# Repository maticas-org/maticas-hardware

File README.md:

# maticas-hardware
Hardware branch of Maticas. Maticas is an  Automated hidroponic system. Project that seeks to create a fully automated hydroponic cultivation system using IoT, with a view to generating an agricultural revolution.

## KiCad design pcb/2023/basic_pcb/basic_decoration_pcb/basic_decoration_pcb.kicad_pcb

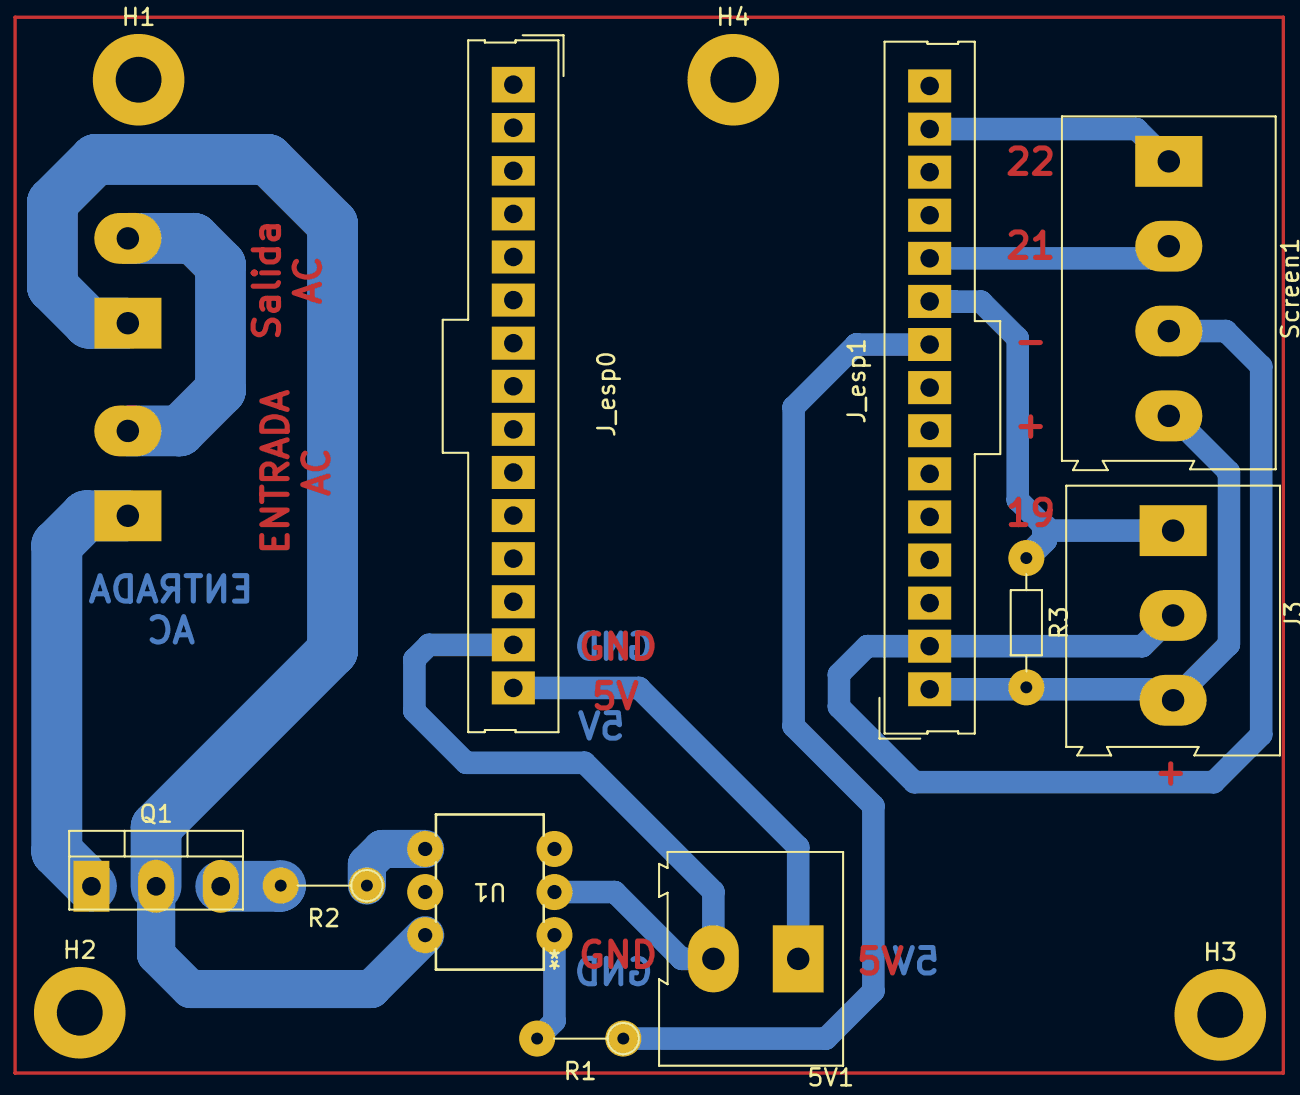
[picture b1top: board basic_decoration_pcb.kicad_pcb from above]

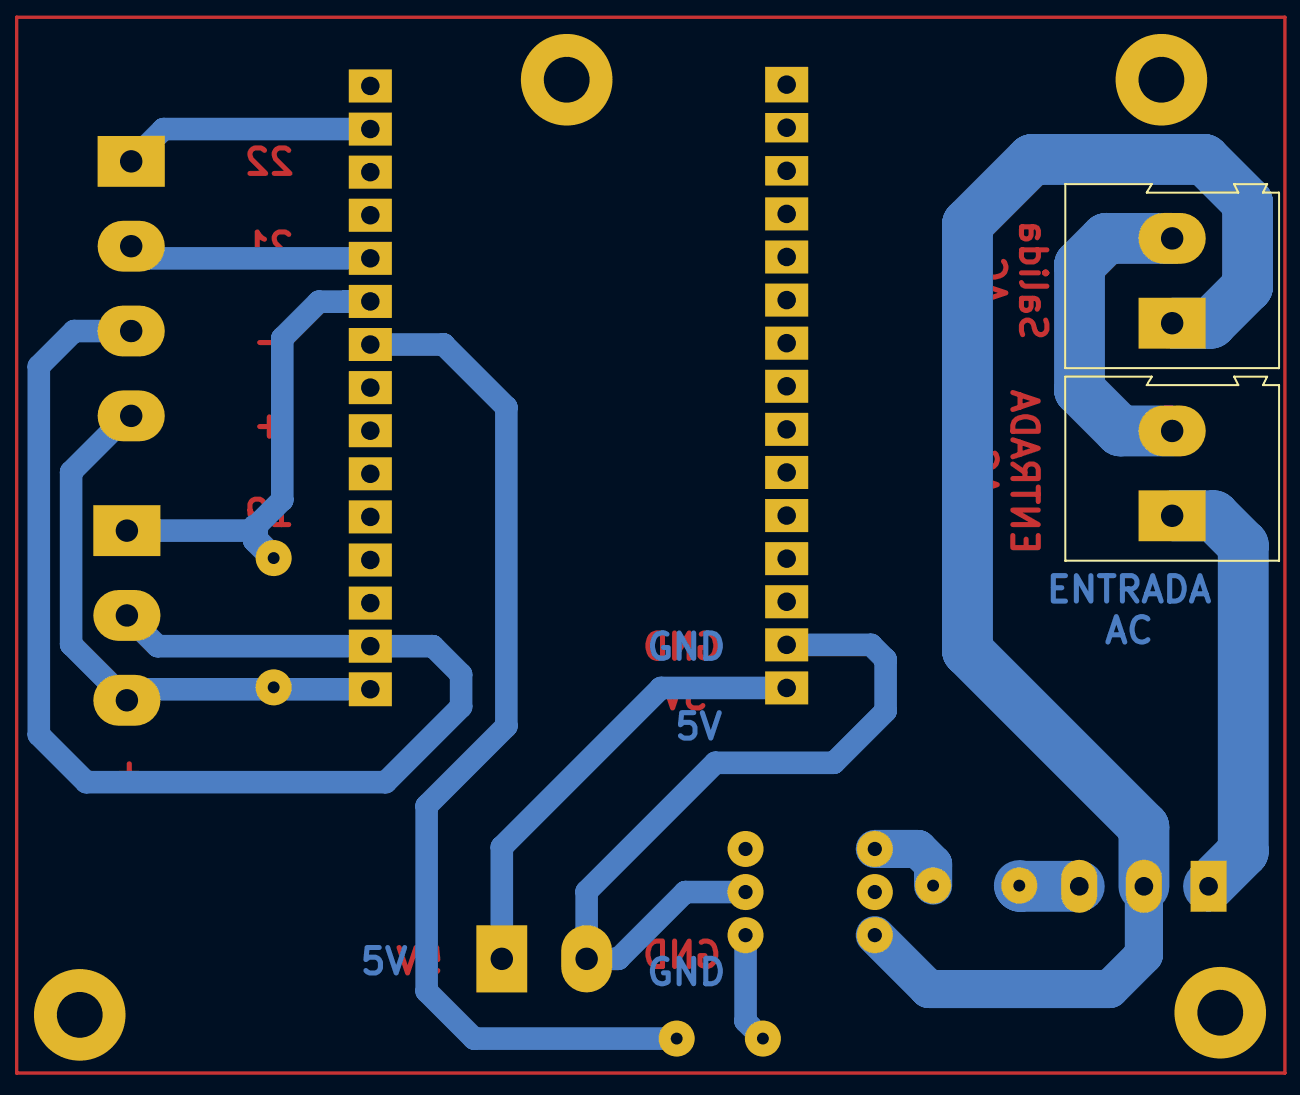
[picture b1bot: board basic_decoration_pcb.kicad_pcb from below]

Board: 2 copper layers, 16 parts (2 on the bottom side), 14 nets.

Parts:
5V1: Screw_Terminal_01x02; TerminalBlock_Altech_AK300-2_P5.00mm
H1, H2, H3, H4: MountingHole; MountingHole_2.7mm_M2.5_Pad
J3: Screw_Terminal_01x03; TerminalBlock_Altech_AK300-3_P5.00mm
J_AC_INPUT1: Screw_Terminal_01x02; TerminalBlock_Altech_AK300-2_P5.00mm
J_AC_LOAD1: Screw_Terminal_01x02; TerminalBlock_Altech_AK300-2_P5.00mm
J_esp0, J_esp1: Conn_01x15_Female; Connector_Molex_Molex_SL_171971-0015_1x15_P2.54mm_Vertical_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
Q1: BT136-500; TO-220-3_Vertical
R1, R2: 470; R_Axial_DIN0204_L3.6mm_D1.6mm_P5.08mm_Vertical
R3: 4.7k_0603; R_Axial_DIN0204_L3.6mm_D1.6mm_P7.62mm_Horizontal
Screen1: Screw_Terminal_01x04; TerminalBlock_Altech_AK300-4_P5.00mm
U1: MOC3041M; PDIP6_6P6X8P89_ONS

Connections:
3V3: J3.3, J_esp1.1, R3.2, Screen1.4
5v: 5V1.1, J_esp0.15
AC1_IN: J_AC_INPUT1.1, Q1.1 (A1)
AC2_IN: J_AC_INPUT1.2, J_AC_LOAD1.2
D18: J_esp1.9, R1.1
D19: J3.1, J_esp1.10, R3.1
D21: J_esp1.11, Screen1.2
D22: J_esp1.14, Screen1.1
GND2: J3.2, J_esp1.2, Screen1.3
GND5V: 5V1.2, J_esp0.14, U1.2
unnamed: J_AC_LOAD1.1, Q1.2 (A2), U1.6
unnamed: Q1.3 (G), R2.2
unnamed: R1.2, U1.1
unnamed: R2.1, U1.4

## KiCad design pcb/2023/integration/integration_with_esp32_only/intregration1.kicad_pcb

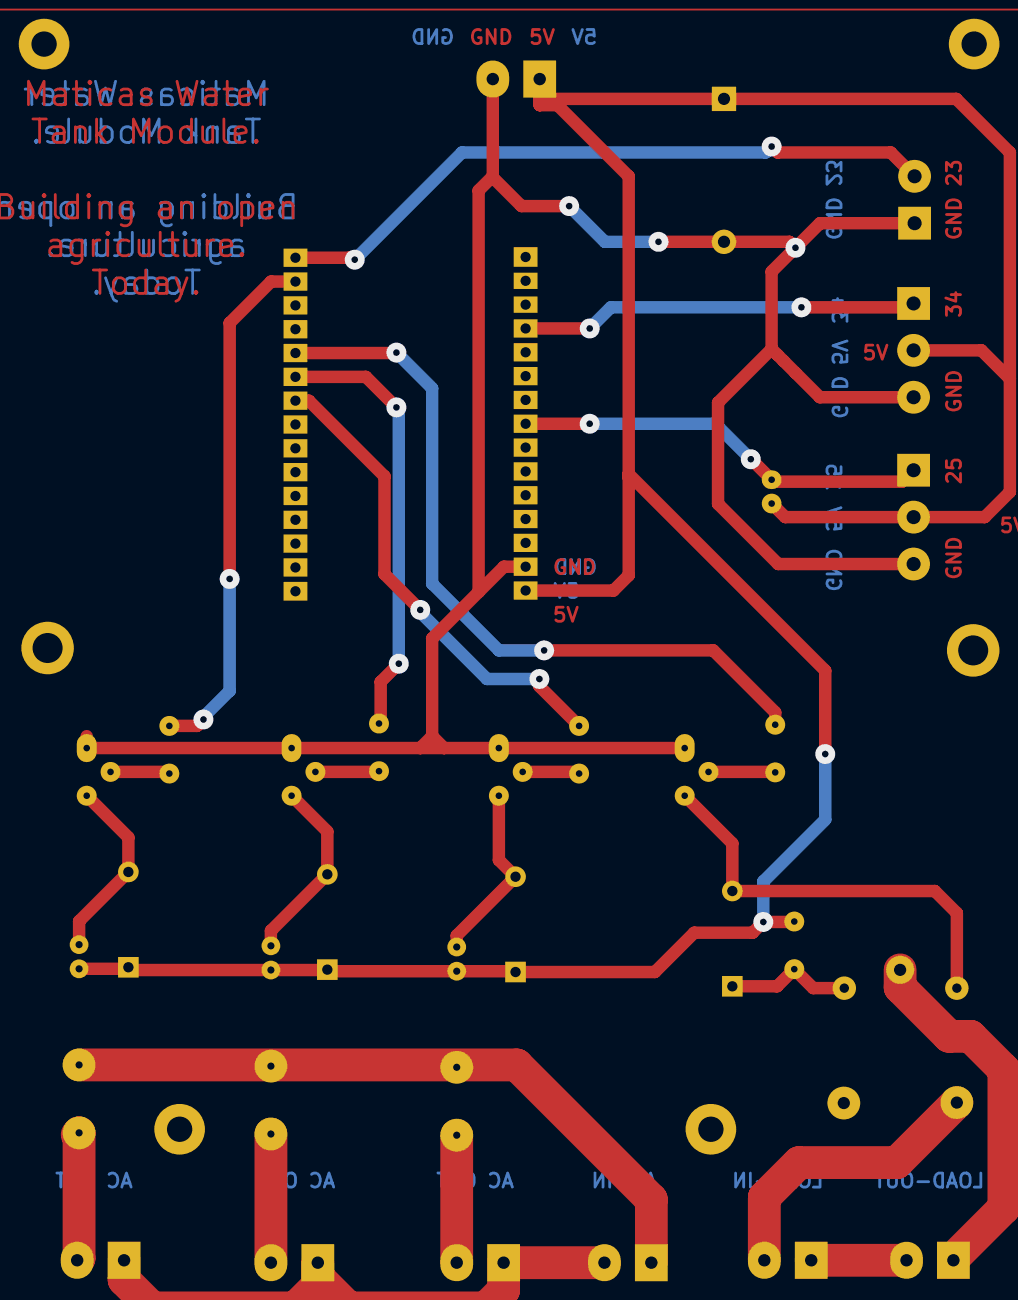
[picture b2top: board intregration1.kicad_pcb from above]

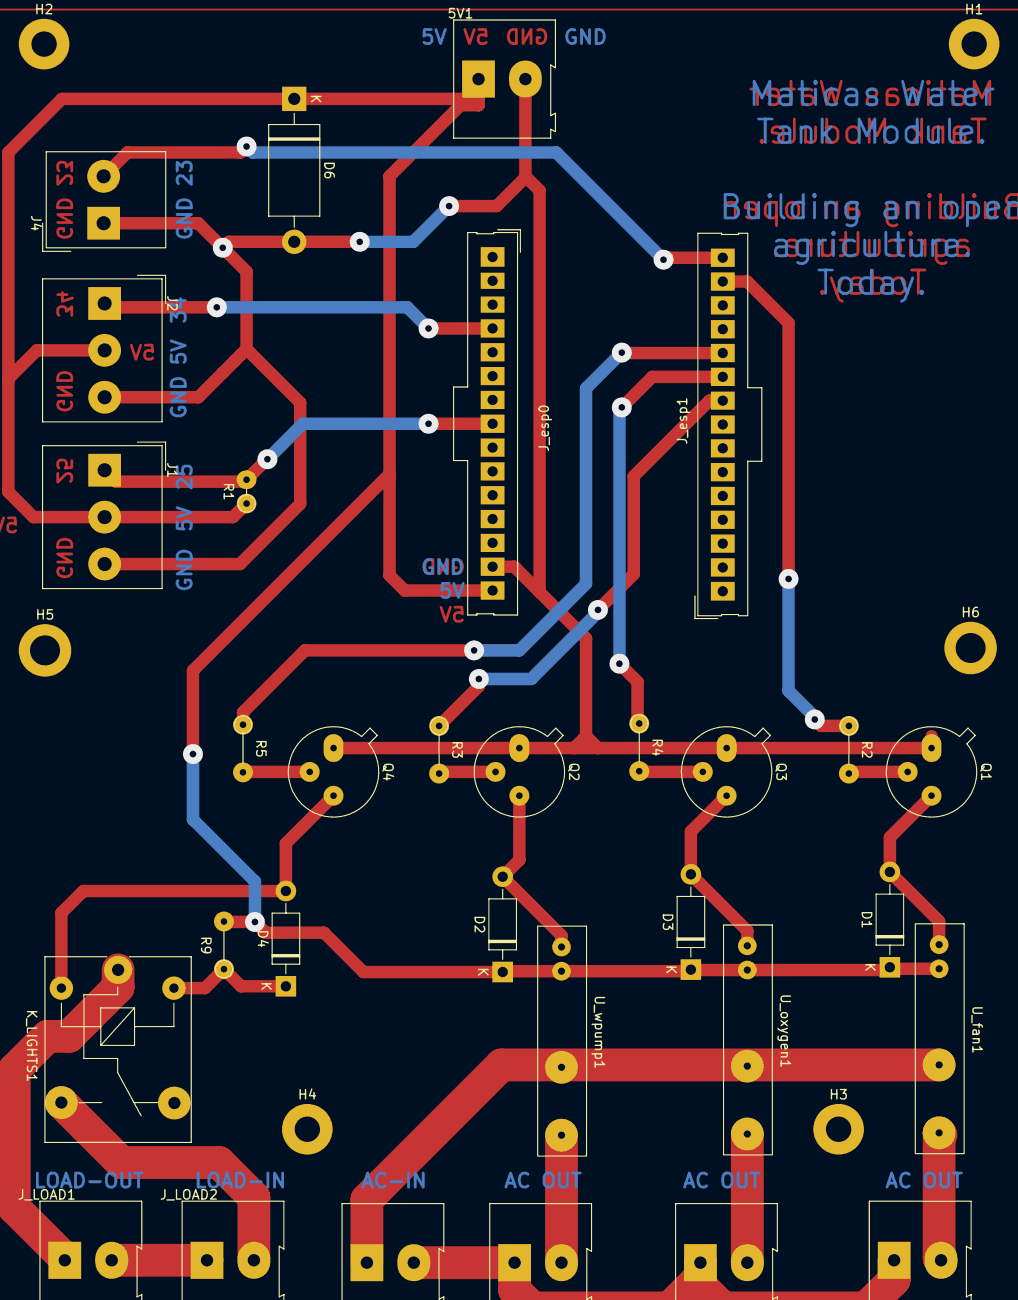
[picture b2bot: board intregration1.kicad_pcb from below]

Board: 2 copper layers, 37 parts (37 on the bottom side), 26 nets.

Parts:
5V1: Screw_Terminal_01x02; TerminalBlock_Altech_AK300-2_P5.00mm
D1, D2, D3, D4: 1N4004; D_DO-41_SOD81_P10.16mm_Horizontal
D6: 1N53xxB; D_DO-201_P15.24mm_Horizontal
H1, H2, H3, H4: MountingHole; MountingHole_2.7mm_M2.5_Pad
H5, H6: MountingHole; MountingHole_3.2mm_M3_DIN965_Pad
J1, J2: Screw_Terminal_01x03; Altech_AK300_1x03_P5.00mm_45-Degree
J4: Screw_Terminal_01x02; Altech_AK300_1x02_P5.00mm_45-Degree
J_AC_INPUT1: Screw_Terminal_01x02; TerminalBlock_Altech_AK300-2_P5.00mm
J_LOAD1, J_LOAD2: Screw_Terminal_01x02; TerminalBlock_Altech_AK300-2_P5.00mm
J_esp0, J_esp1: Conn_01x15_Female; Connector_Molex_Molex_SL_171971-0015_1x15_P2.54mm_Vertical_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
J_fan1: Screw_Terminal_01x02; TerminalBlock_Altech_AK300-2_P5.00mm
J_oxygen1: Screw_Terminal_01x02; TerminalBlock_Altech_AK300-2_P5.00mm
J_wpump1: Screw_Terminal_01x02; TerminalBlock_Altech_AK300-2_P5.00mm
K_LIGHTS1: JQC-3F; Relay_SPDT_SANYOU_SRD_Series_Form_C
Q1, Q2, Q3, Q4: 2N2219; TO-39-3
R1: 4.7k; R_Axial_DIN0204_L3.6mm_D1.6mm_P2.54mm_Vertical
R2, R3, R4, R5: 660; R_Axial_DIN0204_L3.6mm_D1.6mm_P5.08mm_Vertical
R9: 20; R_Axial_DIN0204_L3.6mm_D1.6mm_P5.08mm_Vertical
U_fan1: G3MB-202P
U_oxygen1: G3MB-202P
U_wpump1: G3MB-202P

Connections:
5v: 5V1.1, D1.1 (K), D2.1 (K), D3.1 (K), D6.1 (K), J1.2, J2.2, J_esp0.15, R1.1, R9.2, U_fan1.A1, U_oxygen1.A1, U_wpump1.A1
AC1: J_AC_INPUT1.1, U_fan1.11, U_oxygen1.11, U_wpump1.11
AC2: J_AC_INPUT1.2, J_fan1.1, J_oxygen1.1, J_wpump1.1
D18: J_esp1.9, R3.1
D19: J_esp1.10, R4.1
D21: J_esp1.11, R5.1
D22: J_esp1.14, R2.1
D23: J4.2, J_esp1.15
D25: J1.1, J_esp0.8, R1.2
D34: J2.1, J_esp0.4
GND5V: 5V1.2, D6.2 (A), J1.3, J2.3, J4.1, J_esp0.14, Q1.1 (E), Q2.1 (E), Q3.1 (E), Q4.1 (E)
GND LOAD: J_LOAD1.2, J_LOAD2.1
LOAD IN: J_LOAD1.1, K_LIGHTS1.1
unnamed: D1.2 (A), Q1.3 (C), U_fan1.A2
unnamed: D2.2 (A), Q2.3 (C), U_wpump1.A2
unnamed: D3.2 (A), Q3.3 (C), U_oxygen1.A2
unnamed: D4.2 (A), K_LIGHTS1.2, Q4.3 (C)
unnamed: D4.1 (K), K_LIGHTS1.5, R9.1
unnamed: J_fan1.2, U_fan1.14
unnamed: J_oxygen1.2, U_oxygen1.14
unnamed: J_wpump1.2, U_wpump1.14
unnamed: Q1.2 (B), R2.2
unnamed: Q2.2 (B), R3.2
unnamed: Q3.2 (B), R4.2
unnamed: Q4.2 (B), R5.2
Normally O: J_LOAD2.2, K_LIGHTS1.3

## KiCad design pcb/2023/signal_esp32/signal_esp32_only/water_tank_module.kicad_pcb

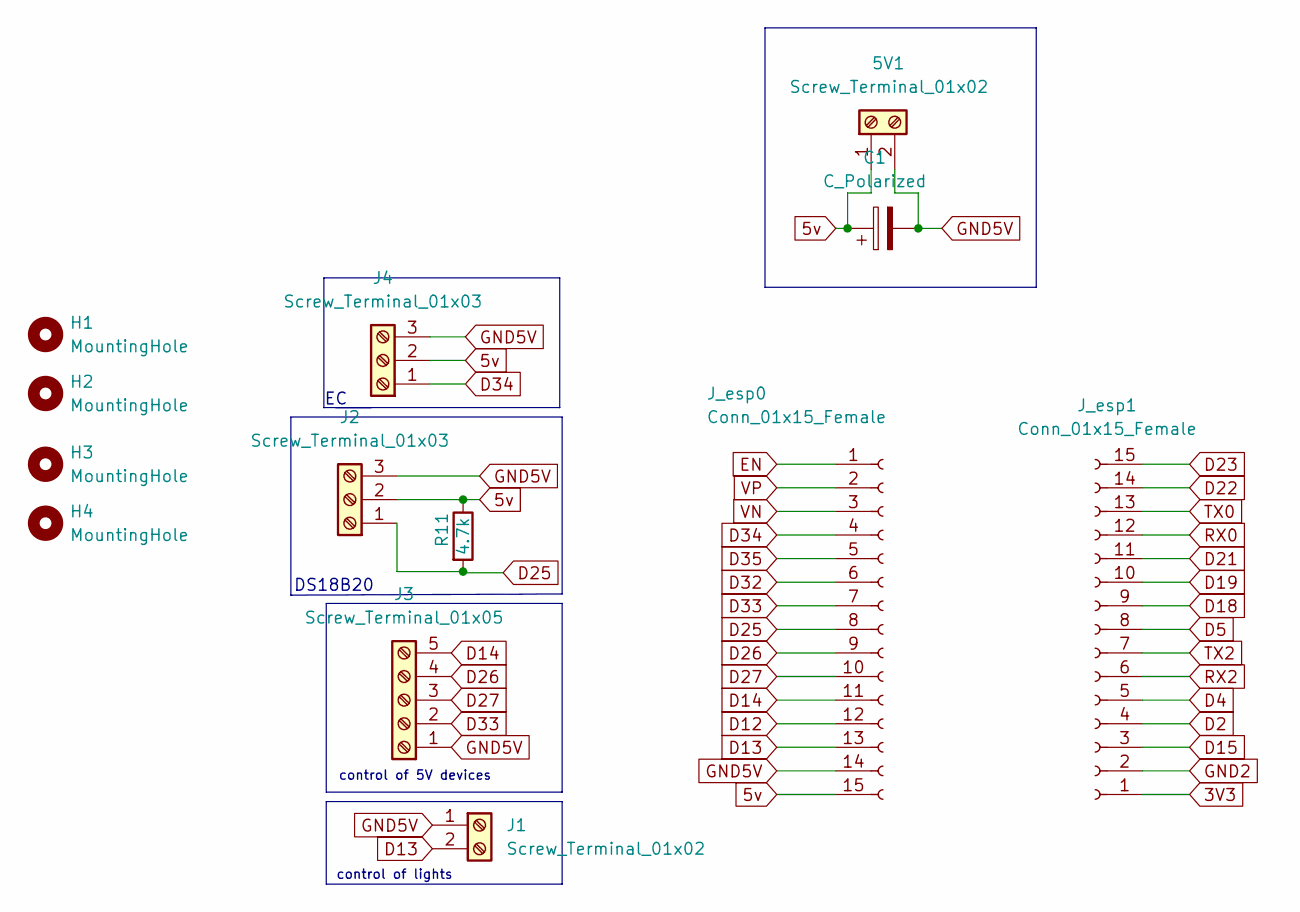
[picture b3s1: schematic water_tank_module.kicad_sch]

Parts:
5V1: Screw_Terminal_01x02; TerminalBlock_Altech_AK300-2_P5.00mm
C1: C_Polarized; CP_Radial_D5.0mm_P2.50mm
H1, H2, H3, H4: MountingHole; MountingHole_2.7mm_M2.5_Pad
J1: Screw_Terminal_01x02; Altech_AK300_1x02_P5.00mm_45-Degree
J2, J4: Screw_Terminal_01x03; Altech_AK300_1x03_P5.00mm_45-Degree
J3: Screw_Terminal_01x05; Altech_AK300_1x05_P5.00mm_45-Degree
J_esp0, J_esp1: Conn_01x15_Female; Connector_Molex_Molex_SL_171971-0015_1x15_P2.54mm_Vertical_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
R11: 4.7k; R_Axial_DIN0204_L3.6mm_D1.6mm_P2.54mm_Vertical

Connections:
3V3: J_esp1.1
5v: 5V1.1, C1.1, J2.2, J4.2, J_esp0.15, R11.1
D2: J_esp1.4
D4: J_esp1.5
D5: J_esp1.8
D12: J_esp0.12
D13: J1.2, J_esp0.13
D14: J3.5, J_esp0.11
D15: J_esp1.3
D18: J_esp1.9
D19: J_esp1.10
D21: J_esp1.11
D22: J_esp1.14
D23: J_esp1.15
D25: J2.1, J_esp0.8, R11.2
D26: J3.4, J_esp0.9
D27: J3.3, J_esp0.10
D32: J_esp0.6
D33: J3.2, J_esp0.7
D34: J4.1, J_esp0.4
D35: J_esp0.5
EN: J_esp0.1
GND2: J_esp1.2
GND5V: 5V1.2, C1.2, J1.1, J2.3, J3.1, J4.3, J_esp0.14
RX0: J_esp1.12
RX2: J_esp1.6
TX0: J_esp1.13
TX2: J_esp1.7
VN: J_esp0.3
VP: J_esp0.2

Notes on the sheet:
control of 5V devices
control of lights
DS18B20

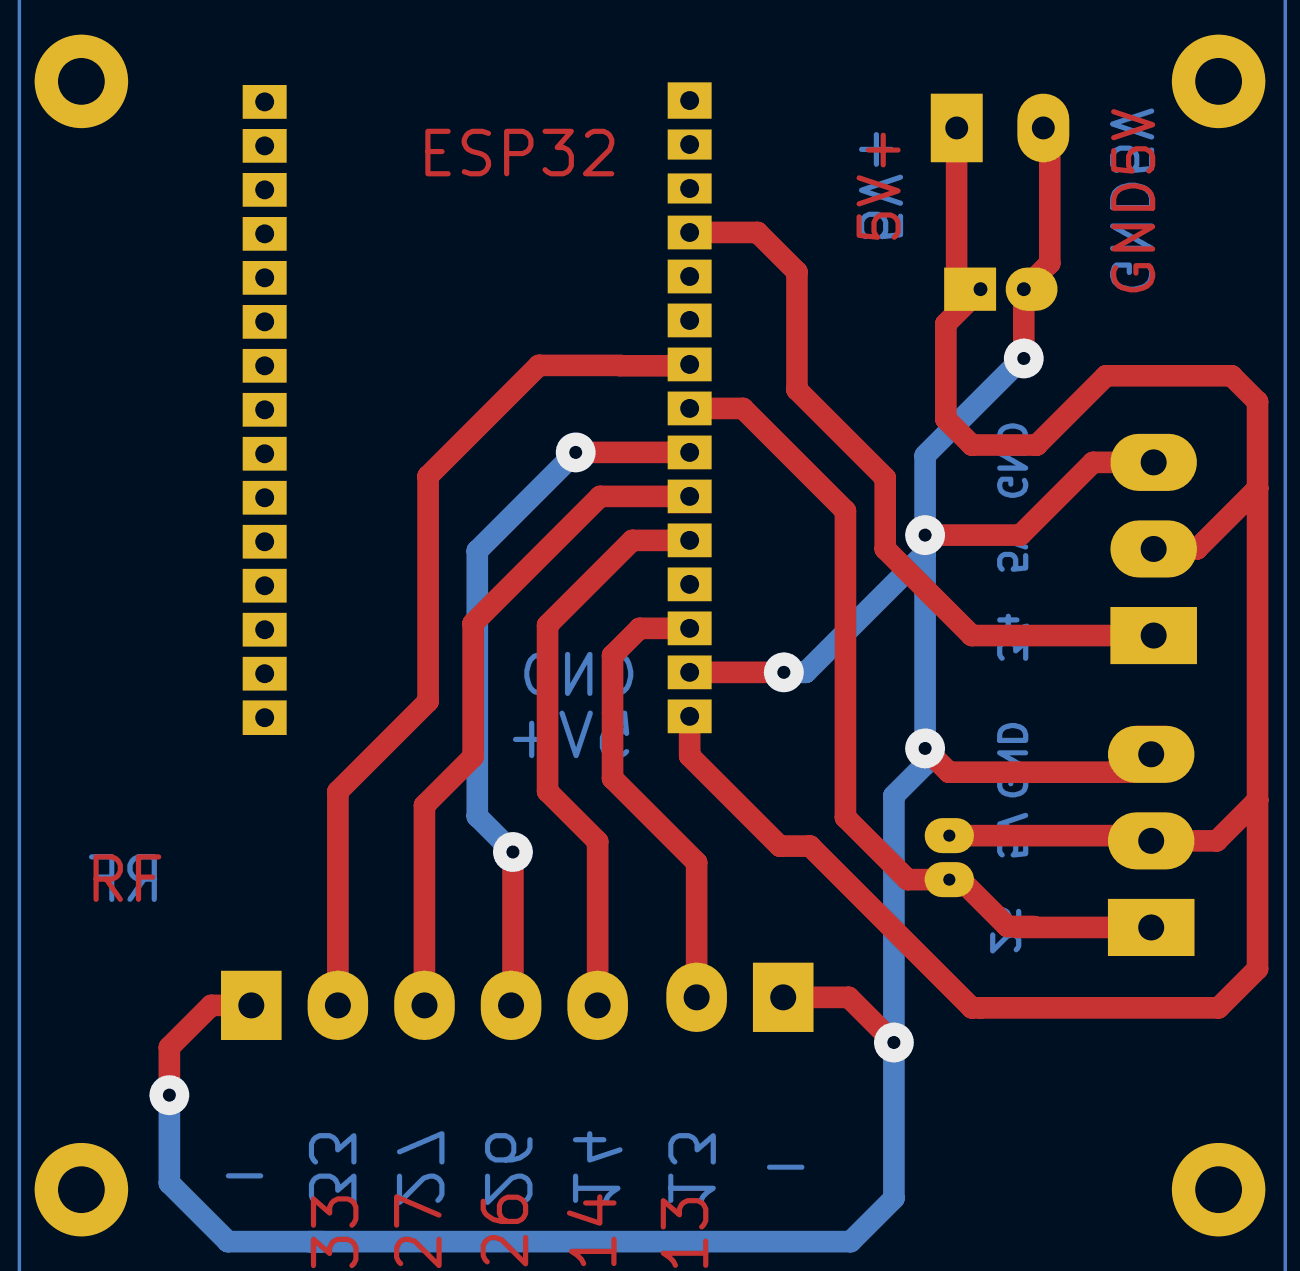
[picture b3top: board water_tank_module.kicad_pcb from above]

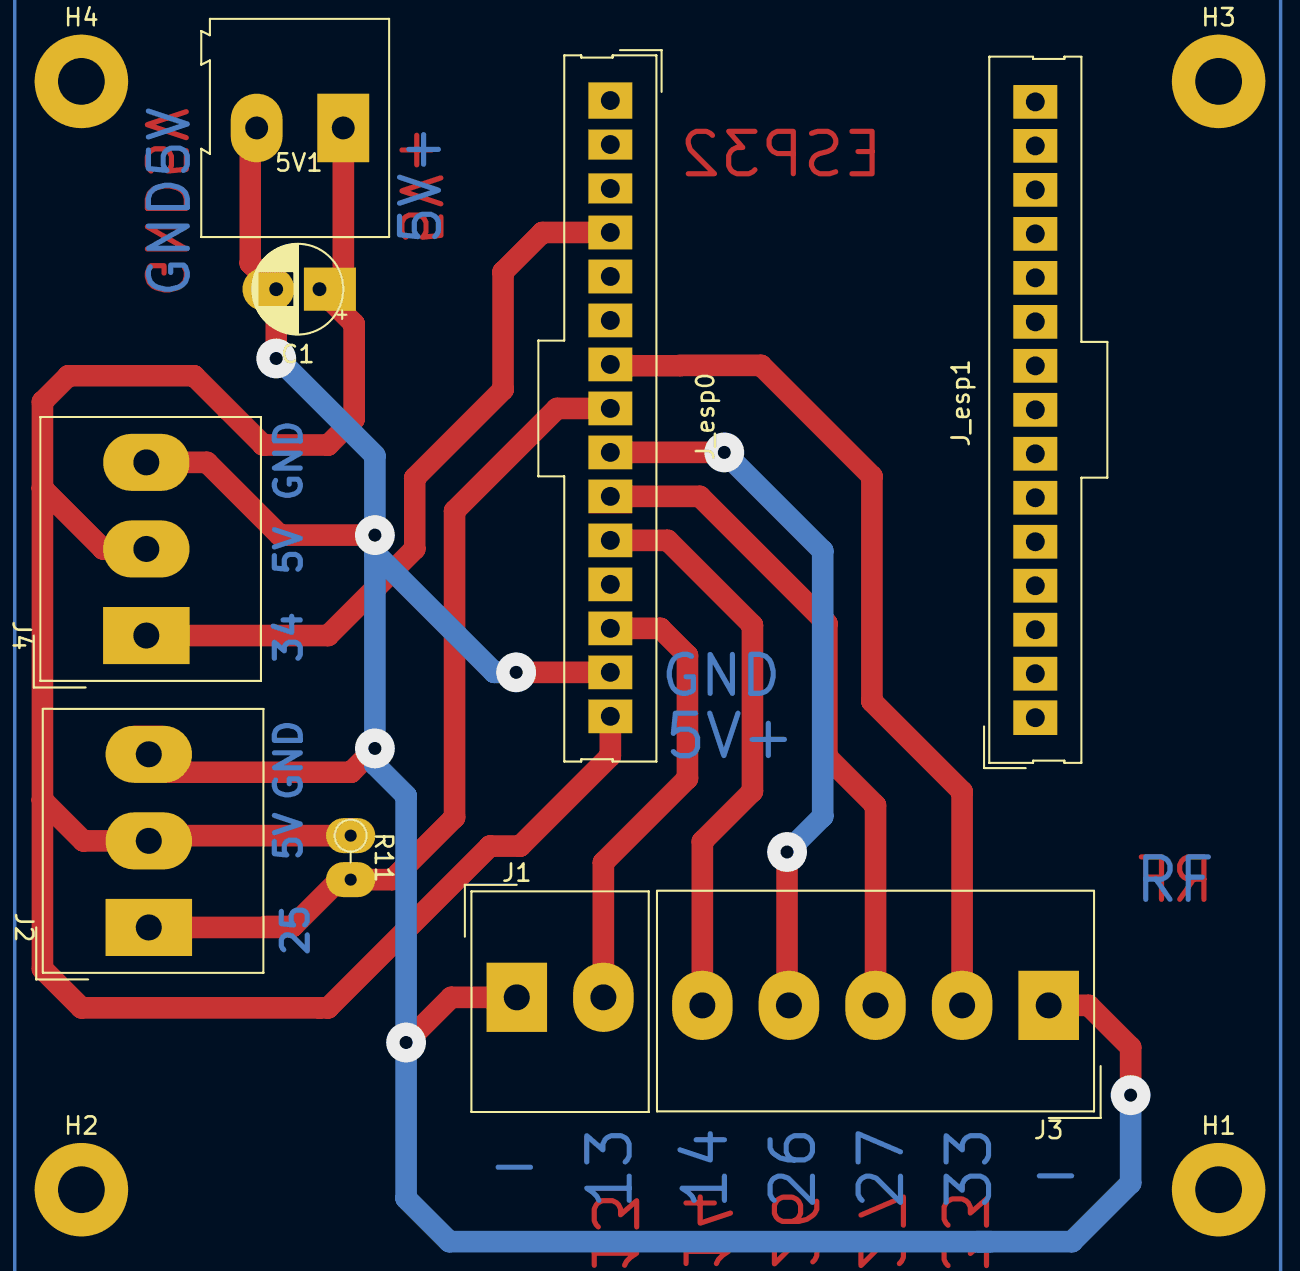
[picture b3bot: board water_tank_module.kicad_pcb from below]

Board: 2 copper layers, 13 parts (13 on the bottom side), 9 nets.

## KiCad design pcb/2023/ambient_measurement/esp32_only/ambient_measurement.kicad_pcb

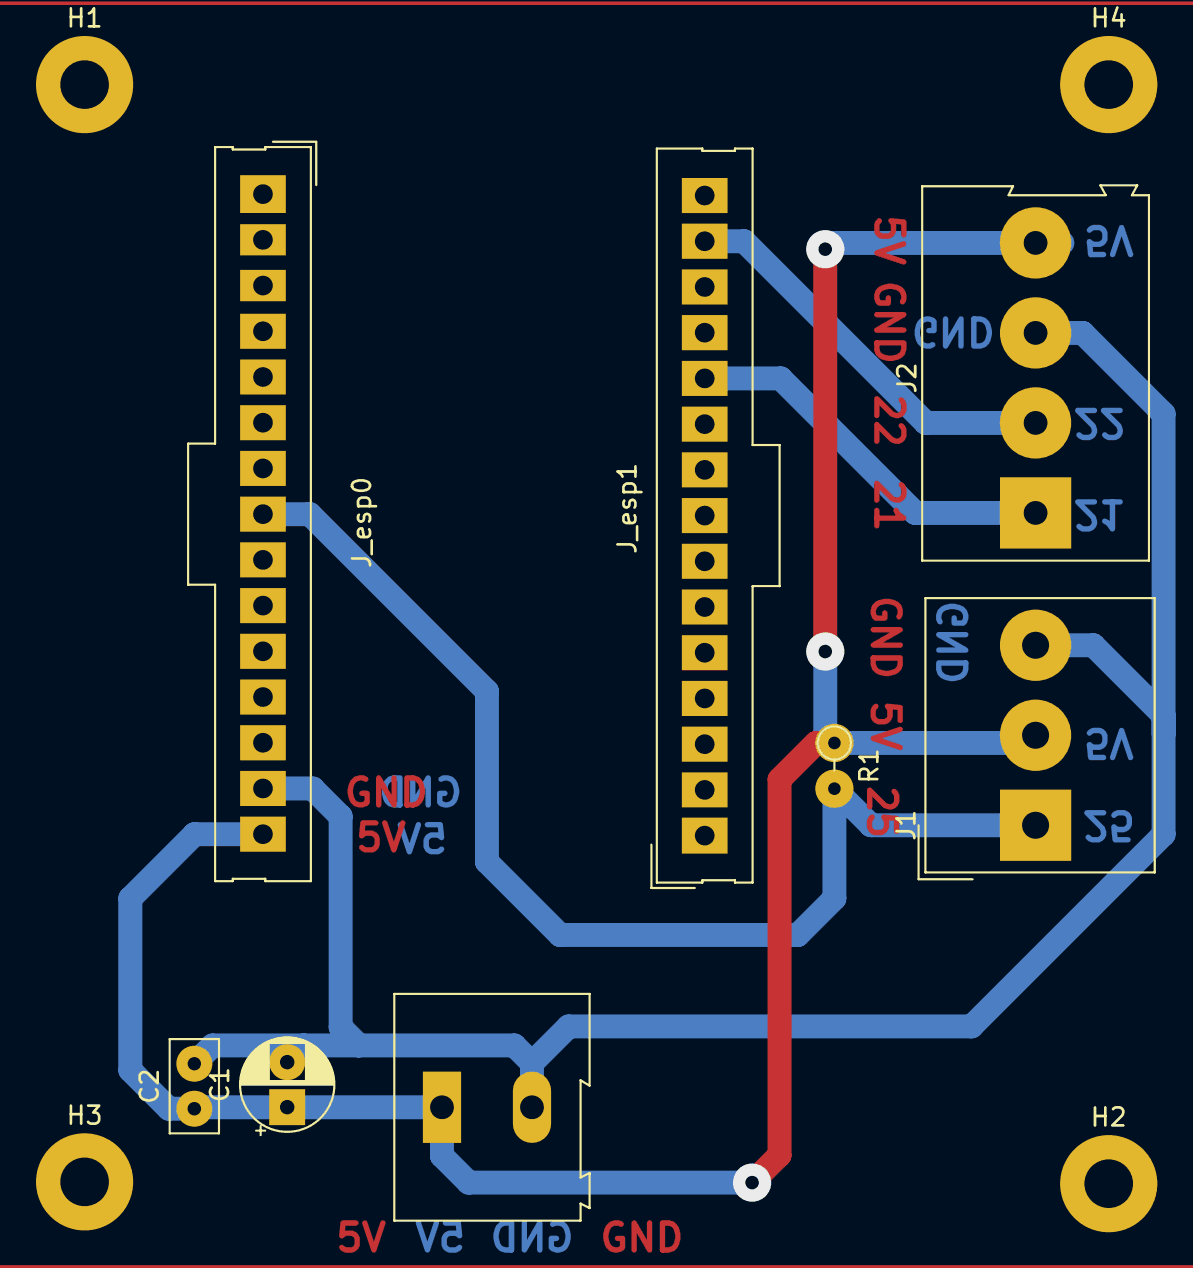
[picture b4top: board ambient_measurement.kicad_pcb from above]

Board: 2 copper layers, 12 parts (0 on the bottom side), 5 nets.

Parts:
5V1: Screw_Terminal_01x02; TerminalBlock_Altech_AK300-2_P5.00mm
C1: C_Polarized; CP_Radial_D5.0mm_P2.50mm
C2: C_Generic; C_Disc_D5.0mm_W2.5mm_P2.50mm
H1, H2, H3, H4: MountingHole; MountingHole_2.7mm_M2.5_Pad
J1: Screw_Terminal_01x03; Altech_AK300_1x03_P5.00mm_45-Degree
J2: Screw_Terminal_01x04; TerminalBlock_Altech_AK300-4_P5.00mm
J_esp0, J_esp1: Conn_01x15_Female; Connector_Molex_Molex_SL_171971-0015_1x15_P2.54mm_Vertical_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
R1: 10k; R_Axial_DIN0204_L3.6mm_D1.6mm_P2.54mm_Vertical

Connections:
5v: 5V1.1, C1.1, C2.1, J1.2, J2.4, J_esp0.15, R1.1
D21: J2.1, J_esp1.11
D22: J2.2, J_esp1.14
D25: J1.1, J_esp0.8, R1.2
GND5V: 5V1.2, C1.2, C2.2, J1.3, J2.3, J_esp0.14

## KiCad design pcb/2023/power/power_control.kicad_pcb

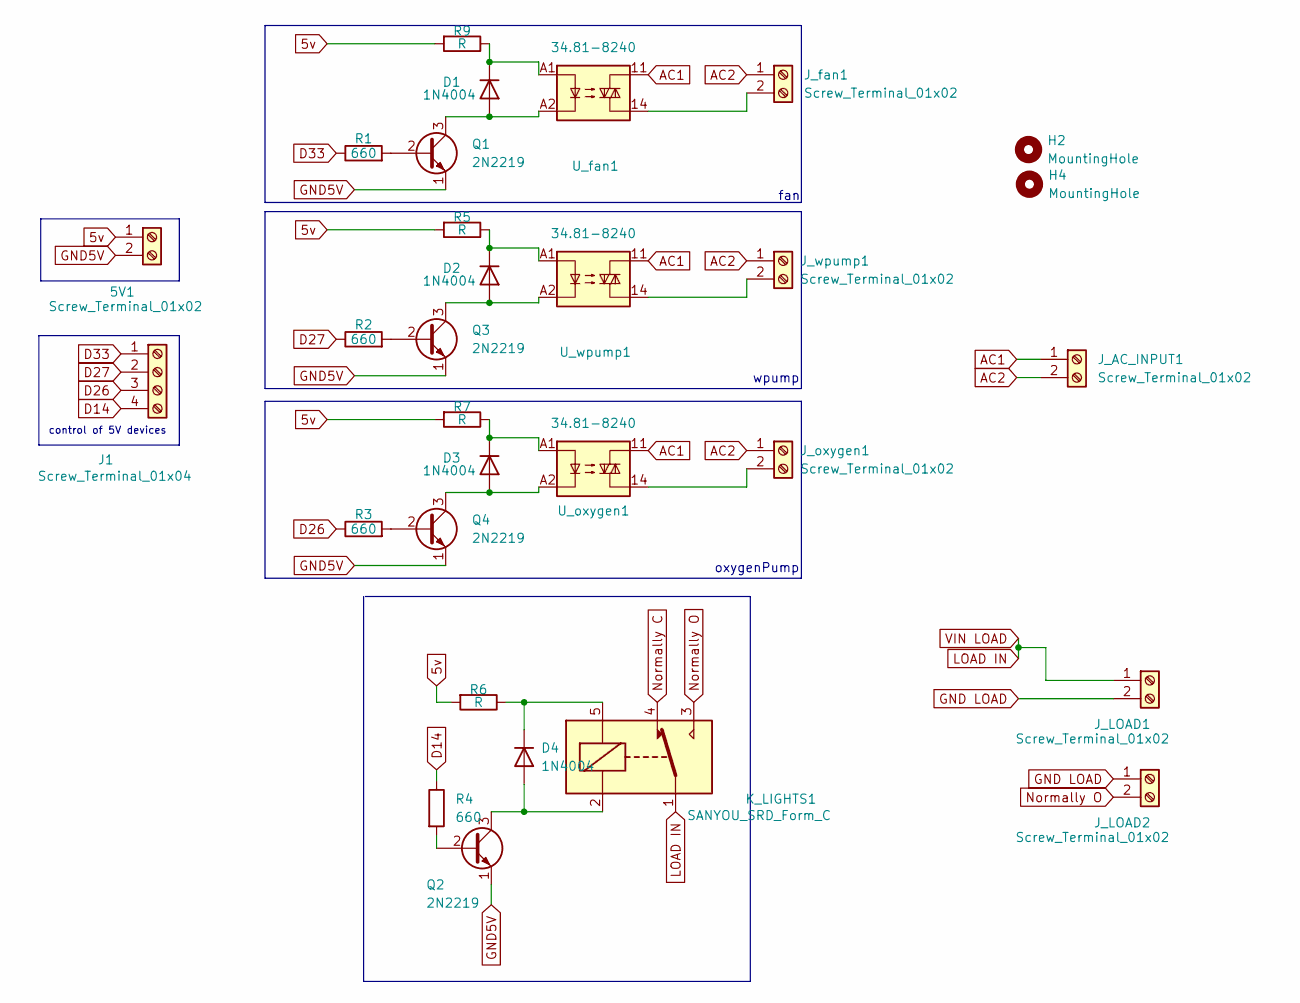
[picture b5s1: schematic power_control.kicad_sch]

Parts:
5V1: Screw_Terminal_01x02; TerminalBlock_Altech_AK300-2_P5.00mm
D1, D2, D3, D4: 1N4004; D_DO-41_SOD81_P10.16mm_Horizontal
H2, H4: MountingHole; MountingHole_3.2mm_M3_DIN965_Pad
J1: Screw_Terminal_01x04; Altech_AK300_1x04_P5.00mm_45-Degree
J_AC_INPUT1: Screw_Terminal_01x02; TerminalBlock_Altech_AK300-2_P5.00mm
J_LOAD1, J_LOAD2: Screw_Terminal_01x02; TerminalBlock_Altech_AK300-2_P5.00mm
J_fan1: Screw_Terminal_01x02; TerminalBlock_Altech_AK300-2_P5.00mm
J_oxygen1: Screw_Terminal_01x02; TerminalBlock_Altech_AK300-2_P5.00mm
J_wpump1: Screw_Terminal_01x02; TerminalBlock_Altech_AK300-2_P5.00mm
K_LIGHTS1: SANYOU_SRD_Form_C; Relay_SPDT_SANYOU_SRD_Series_Form_C
Q1, Q2, Q3, Q4: 2N2219; TO-39-3
R1, R2, R3, R4: 660; R_Axial_DIN0204_L3.6mm_D1.6mm_P5.08mm_Vertical
R5, R6, R7, R9: R; R_Axial_DIN0204_L3.6mm_D1.6mm_P5.08mm_Vertical
U_fan1: 34.81-8240; G3MB-202P
U_oxygen1: 34.81-8240; G3MB-202P
U_wpump1: 34.81-8240; G3MB-202P

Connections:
5v: 5V1.1, R5.2, R6.2, R7.2, R9.2
AC1: J_AC_INPUT1.1, U_fan1.11, U_oxygen1.11, U_wpump1.11
AC2: J_AC_INPUT1.2, J_fan1.1, J_oxygen1.1, J_wpump1.1
D14: J1.4, R4.1
D26: J1.3, R3.1
D27: J1.2, R2.1
D33: J1.1, R1.1
GND5V: 5V1.2, Q1.1 (E), Q2.1 (E), Q3.1 (E), Q4.1 (E)
GND LOAD: J_LOAD1.2, J_LOAD2.1
LOAD IN: J_LOAD1.1, K_LIGHTS1.1
unnamed: D1.1 (K), R9.1, U_fan1.A1
unnamed: D1.2 (A), Q1.3 (C), U_fan1.A2
unnamed: D2.1 (K), R5.1, U_wpump1.A1
unnamed: D2.2 (A), Q3.3 (C), U_wpump1.A2
unnamed: D3.1 (K), R7.1, U_oxygen1.A1
unnamed: D3.2 (A), Q4.3 (C), U_oxygen1.A2
unnamed: D4.1 (K), K_LIGHTS1.5, R6.1
unnamed: D4.2 (A), K_LIGHTS1.2, Q2.3 (C)
unnamed: J_fan1.2, U_fan1.14
unnamed: J_oxygen1.2, U_oxygen1.14
unnamed: J_wpump1.2, U_wpump1.14
unnamed: Q1.2 (B), R1.2
unnamed: Q2.2 (B), R4.2
unnamed: Q3.2 (B), R2.2
unnamed: Q4.2 (B), R3.2
Normally C: K_LIGHTS1.4
Normally O: J_LOAD2.2, K_LIGHTS1.3

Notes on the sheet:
fan
wpump
oxygenPump
control of 5V devices

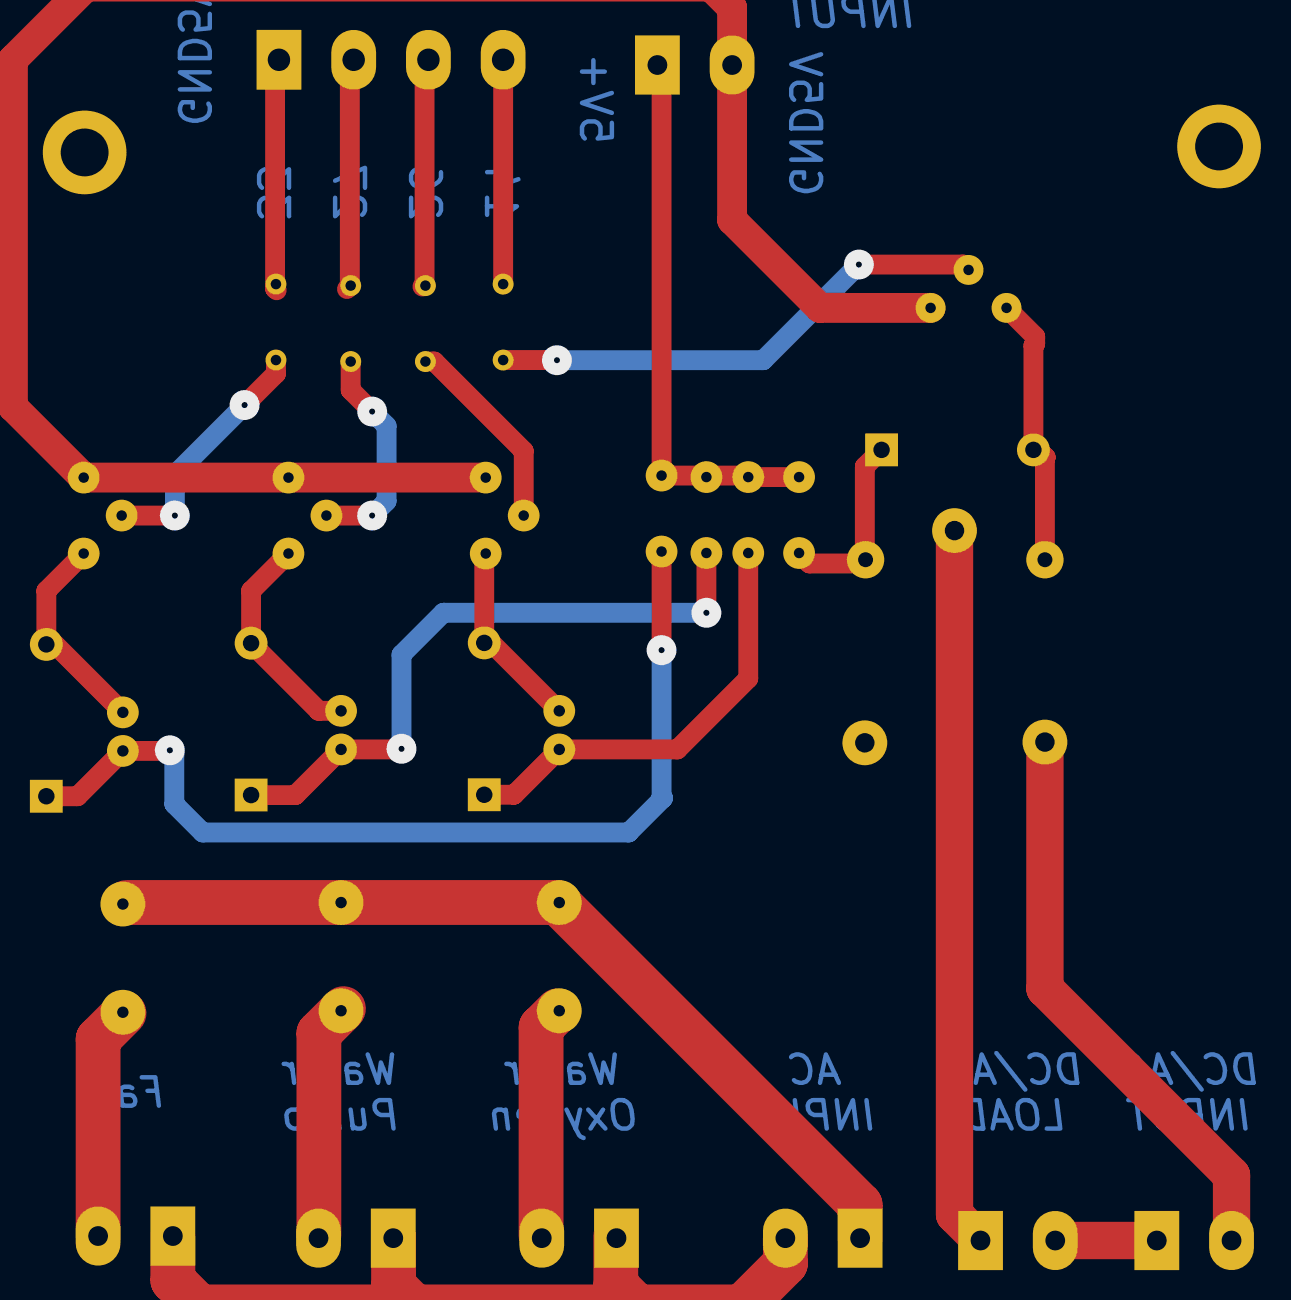
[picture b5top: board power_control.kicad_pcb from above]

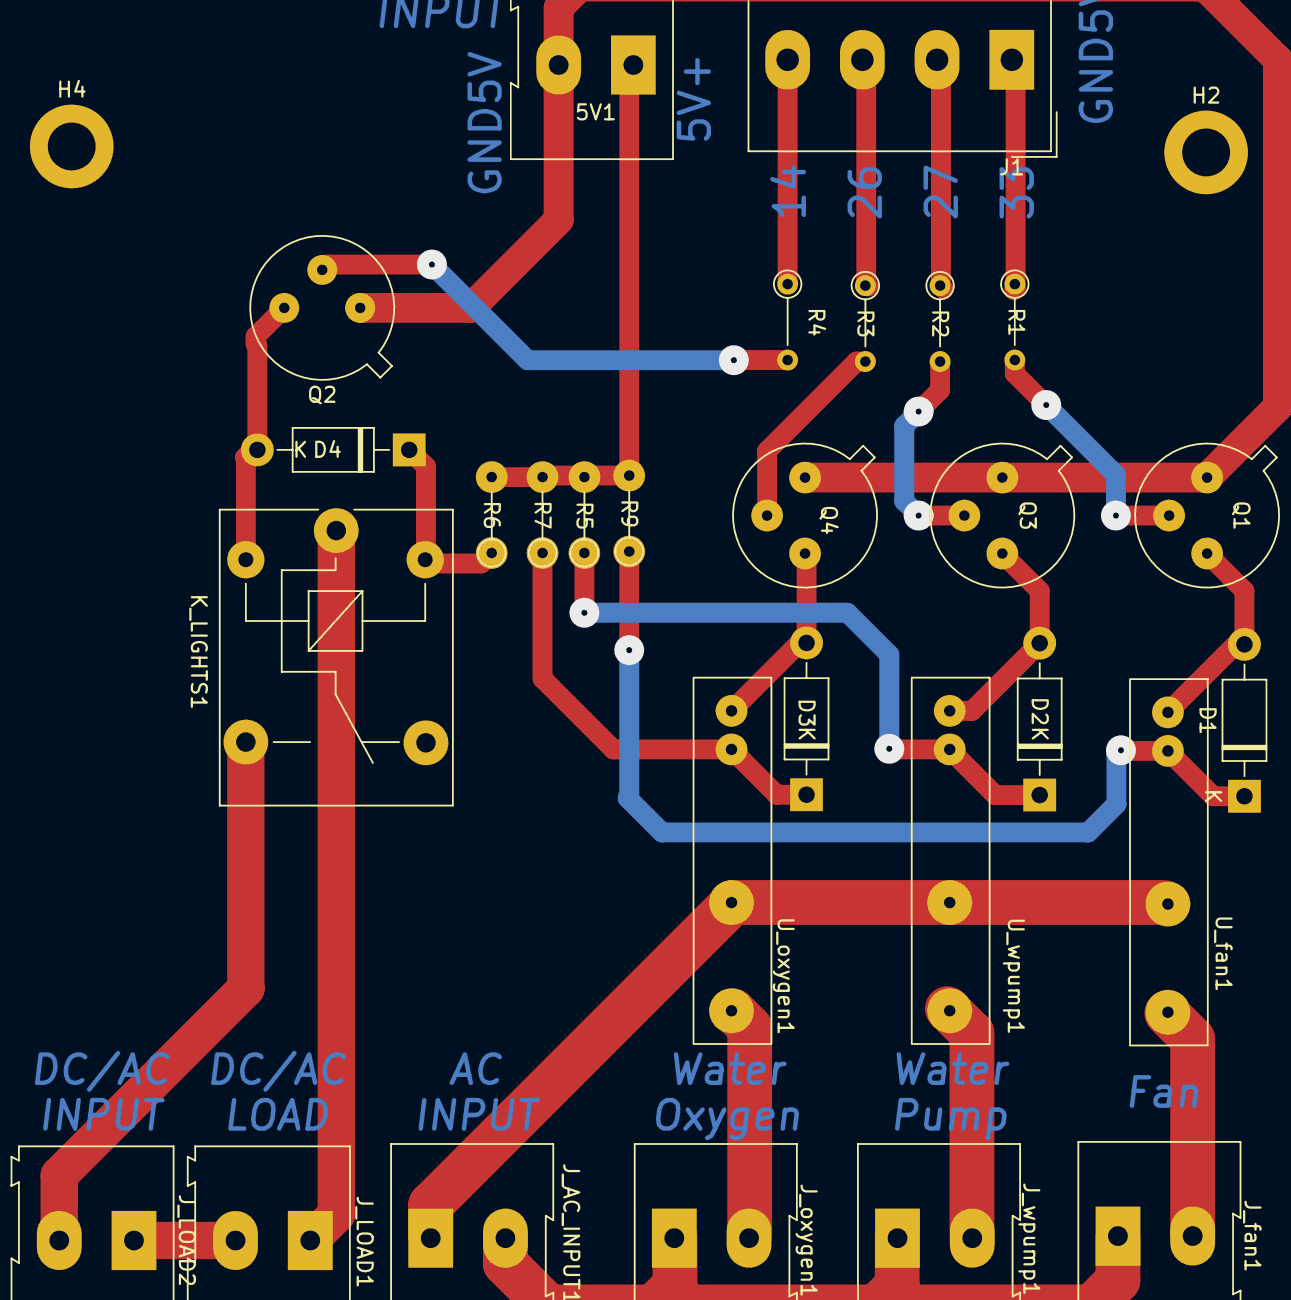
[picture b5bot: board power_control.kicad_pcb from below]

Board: 2 copper layers, 30 parts (30 on the bottom side), 26 nets.

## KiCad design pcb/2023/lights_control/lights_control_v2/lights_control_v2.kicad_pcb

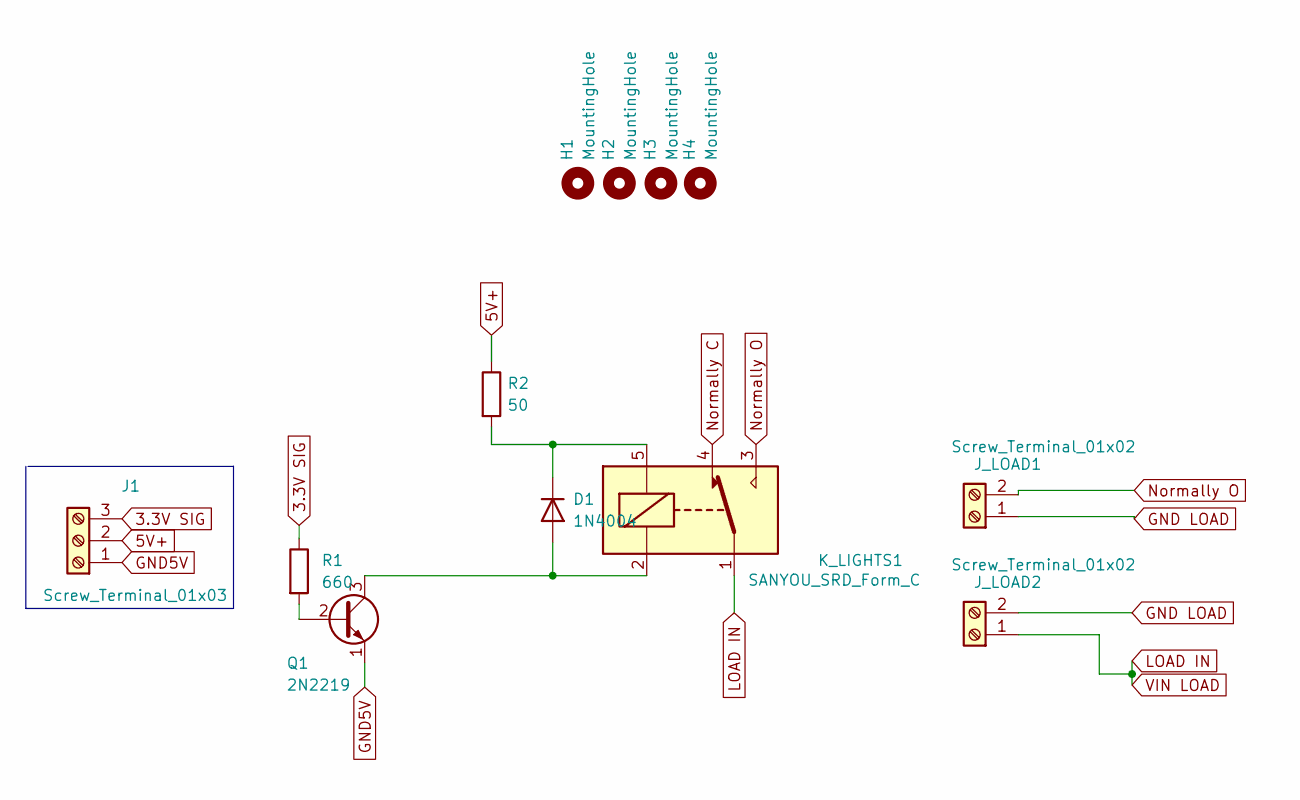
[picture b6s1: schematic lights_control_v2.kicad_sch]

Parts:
D1: 1N4004; D_DO-41_SOD81_P10.16mm_Horizontal
H1, H2, H3, H4: MountingHole; MountingHole_4.3mm_M4_DIN965_Pad
J1: Screw_Terminal_01x03; TerminalBlock_Altech_AK300-3_P5.00mm
J_LOAD1, J_LOAD2: Screw_Terminal_01x02; TerminalBlock_Altech_AK300-2_P5.00mm
K_LIGHTS1: SANYOU_SRD_Form_C; Relay_SPDT_SANYOU_SRD_Series_Form_C
Q1: 2N2219; TO-39-3
R1: 660; R_Axial_DIN0204_L3.6mm_D1.6mm_P2.54mm_Vertical
R2: 50; R_Axial_DIN0204_L3.6mm_D1.6mm_P2.54mm_Vertical

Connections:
3.3V SIG: J1.3, R1.1
5V+: J1.2, R2.1
GND5V: J1.1, Q1.1 (E)
GND LOAD: J_LOAD1.1, J_LOAD2.2
LOAD IN: J_LOAD2.1, K_LIGHTS1.1
unnamed: D1.1 (K), K_LIGHTS1.5, R2.2
unnamed: D1.2 (A), K_LIGHTS1.2, Q1.3 (C)
unnamed: Q1.2 (B), R1.2
Normally C: K_LIGHTS1.4
Normally O: J_LOAD1.2, K_LIGHTS1.3
